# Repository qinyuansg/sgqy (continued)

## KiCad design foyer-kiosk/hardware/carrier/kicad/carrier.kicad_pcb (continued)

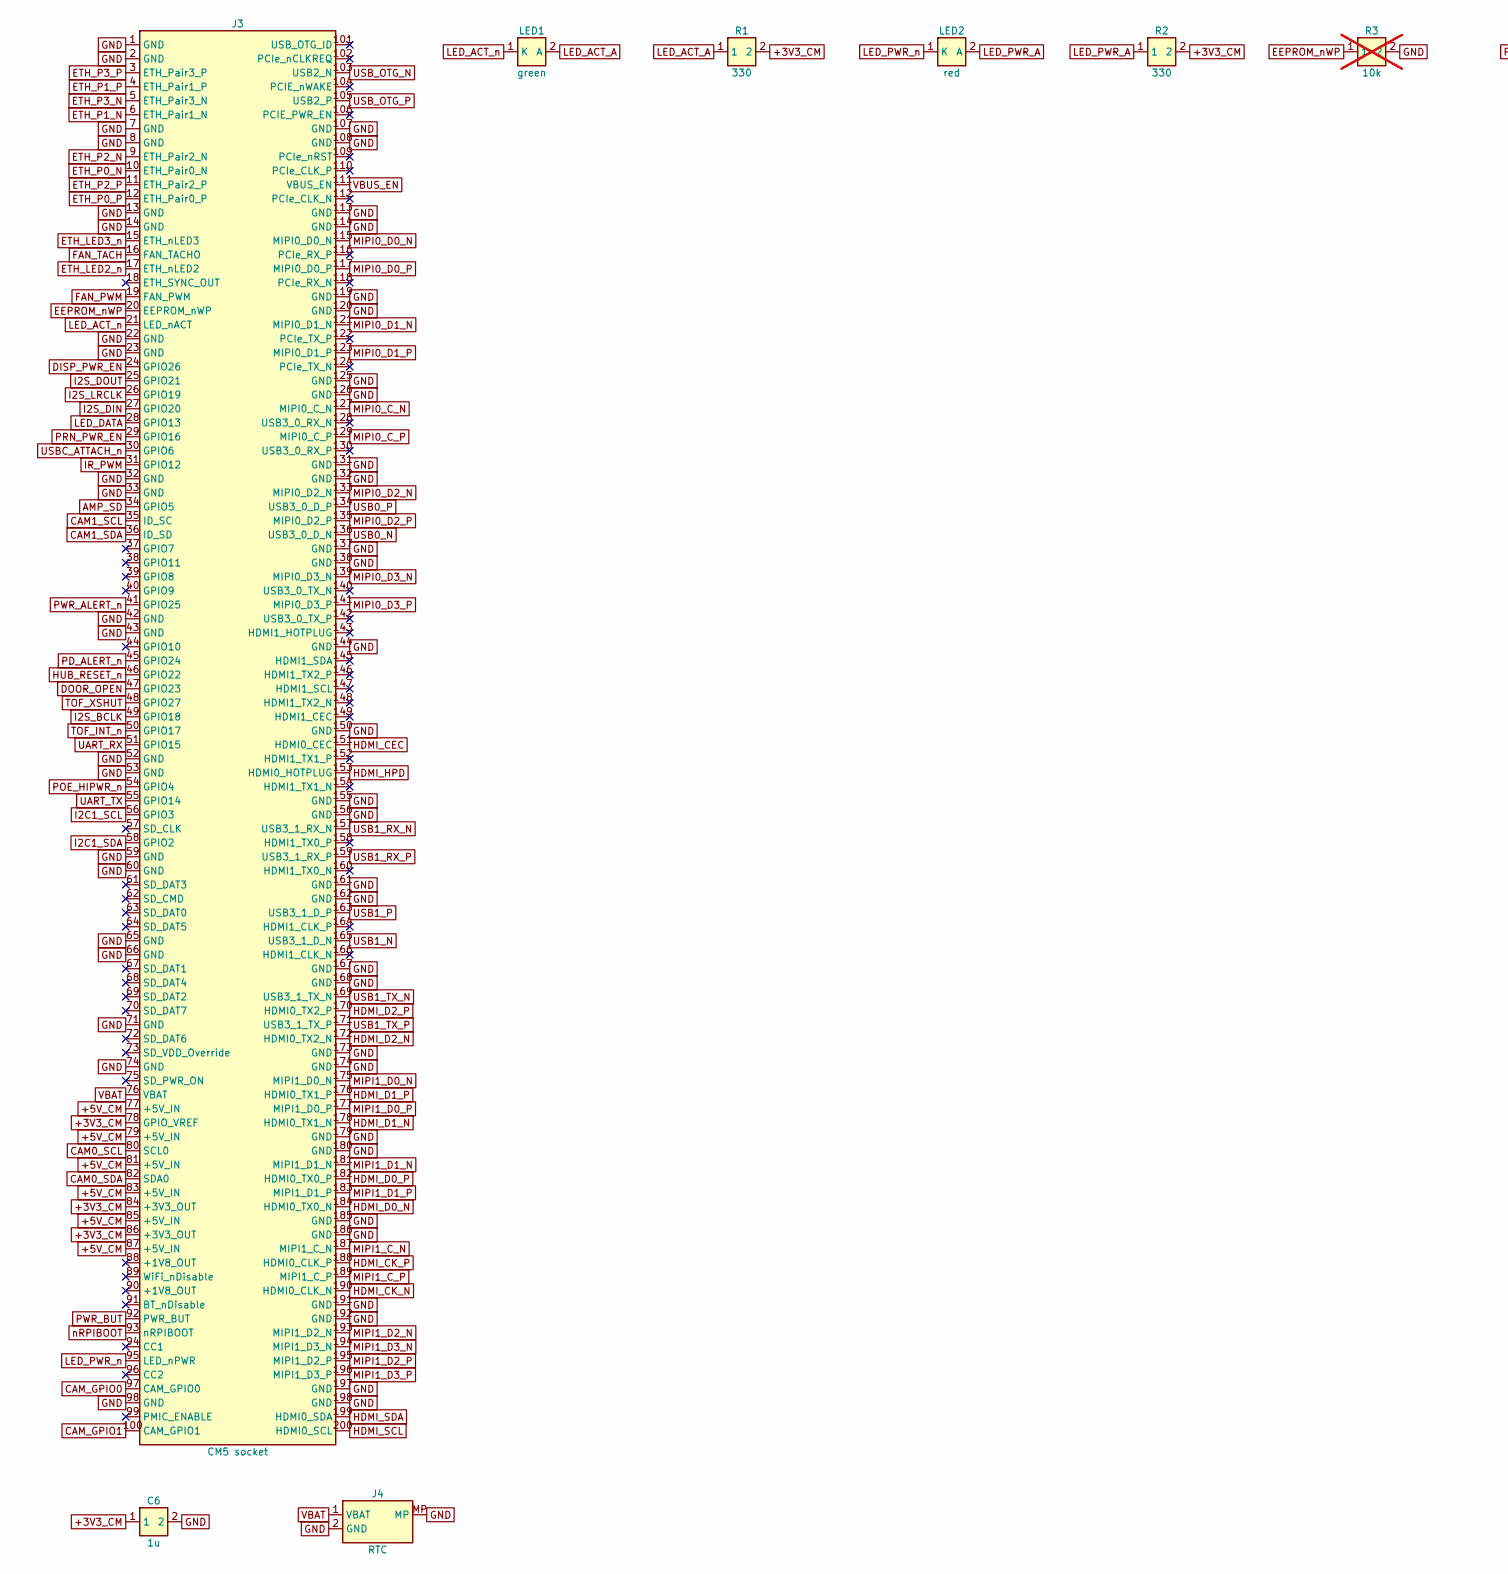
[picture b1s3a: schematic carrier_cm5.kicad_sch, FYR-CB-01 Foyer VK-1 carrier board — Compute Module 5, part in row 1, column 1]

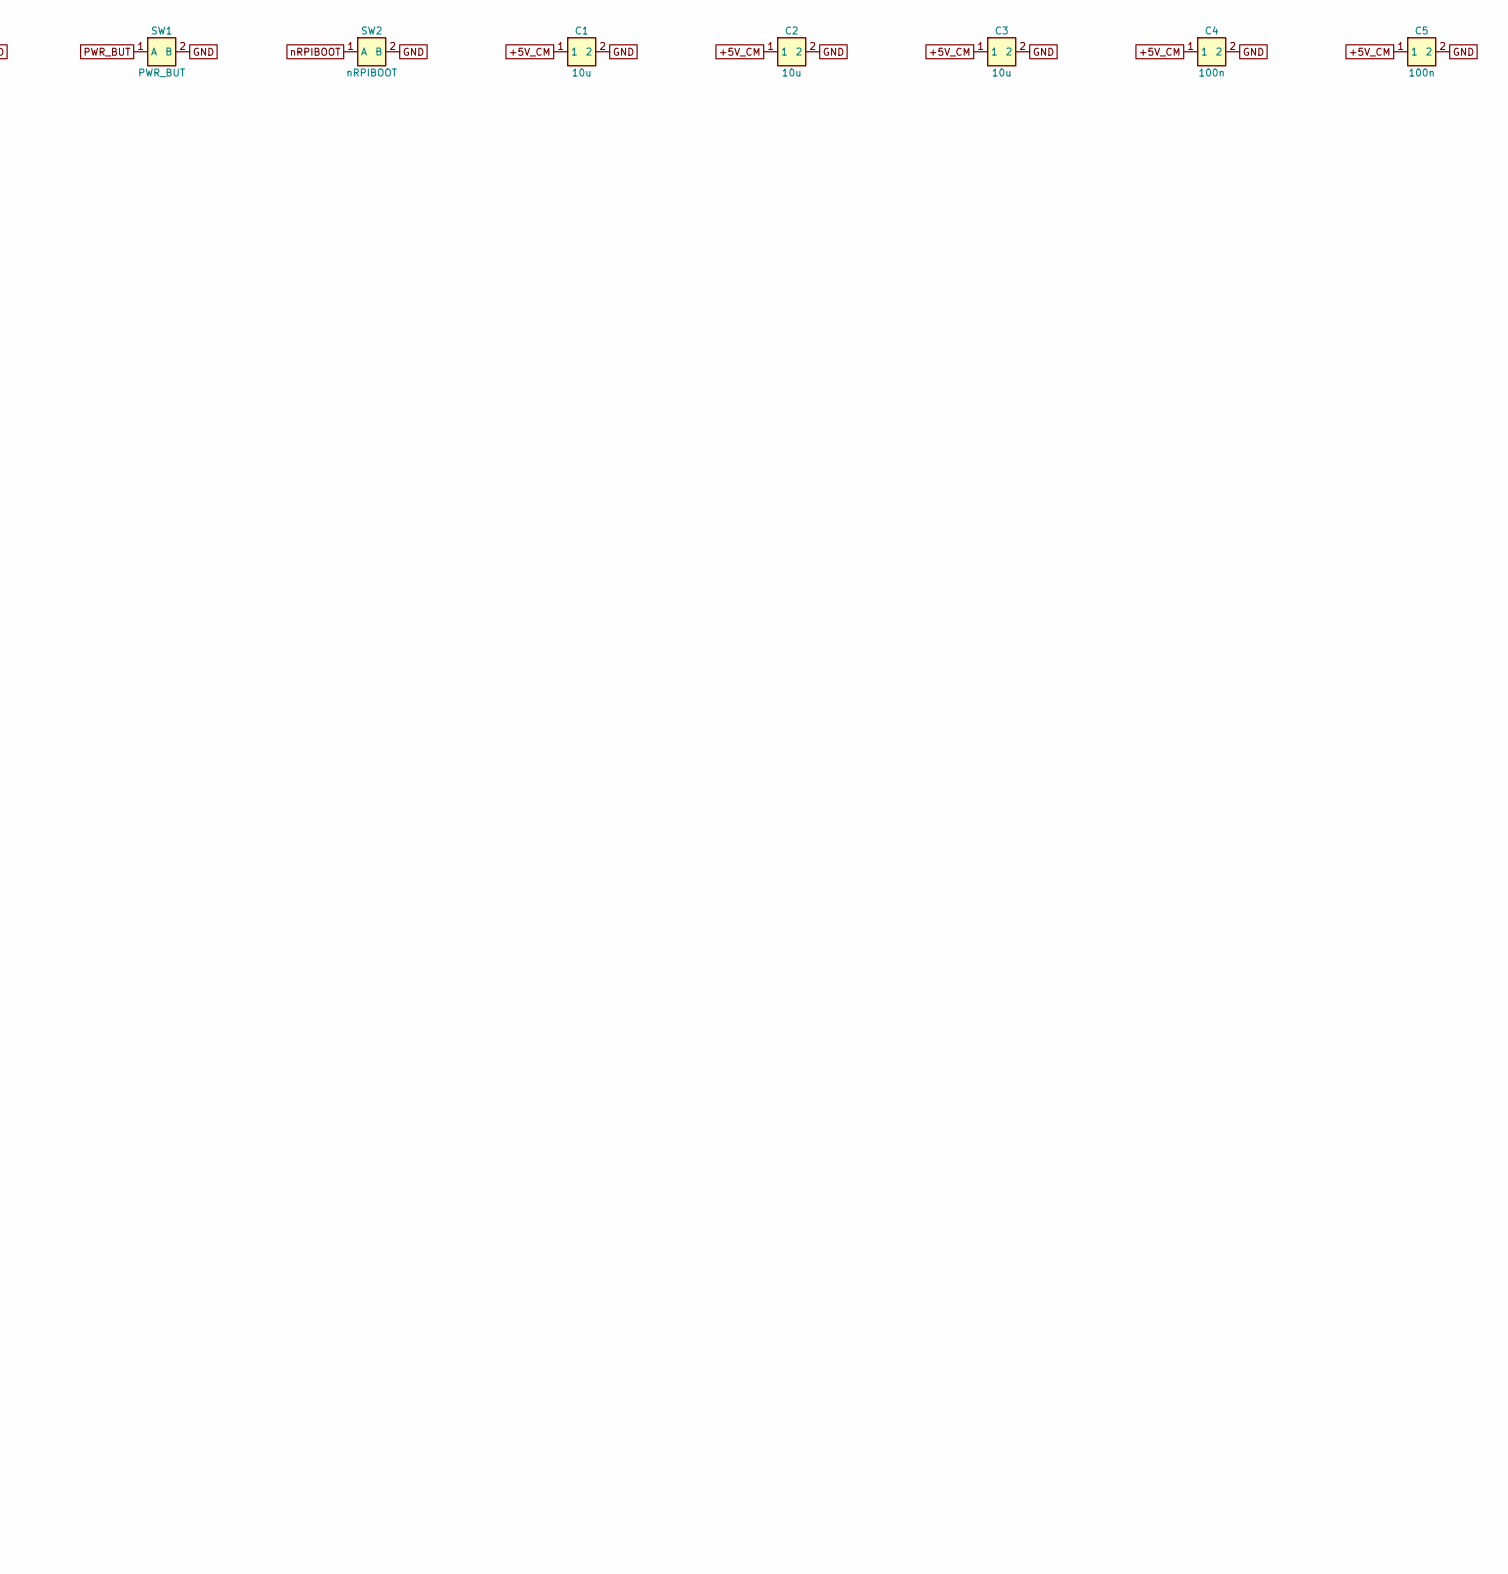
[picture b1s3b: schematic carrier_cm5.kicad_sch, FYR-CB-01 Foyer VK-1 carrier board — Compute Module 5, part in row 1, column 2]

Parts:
C1, C2, C3: 10u; C_0805_2012Metric
C4, C5: 100n; C_0805_2012Metric
C6: 1u; C_0402_1005Metric
J3: CM5 socket; RPi_CM5_DF40C-100DS_Pair; MPN DF40C-100DS-0.4V(51)
J4: RTC; JST_SH_SM02B-SRSS-TB_1x02-1MP_P1.00mm_Horizontal; MPN SM02B-SRSS-TB
LED1: green; LED_0603_1608Metric; MPN LTST-C191KGKT
LED2: red; LED_0603_1608Metric; MPN LTST-C191KRKT
R1, R2: 330; R_0402_1005Metric
R3: 10k; R_0402_1005Metric; not fitted
SW1: PWR_BUT; SW_Push_1P1T_NO_CK_KMR2; MPN KMR221GLFS
SW2: nRPIBOOT; SW_Push_1P1T_NO_CK_KMR2; MPN KMR221GLFS

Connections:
+3V3_CM: C6.1, J3.78 (GPIO_VREF), J3.84 (+3V3_OUT), J3.86 (+3V3_OUT), R1.2, R2.2; also elsewhere on the board
+5V_CM: C1.1, C2.1, C3.1, C4.1, C5.1, J3.77 (+5V_IN), J3.79 (+5V_IN), J3.81 (+5V_IN), J3.83 (+5V_IN), J3.85 (+5V_IN), J3.87 (+5V_IN); also elsewhere on the board
AMP_SD: J3.34 (GPIO5); also elsewhere on the board
CAM0_SCL: J3.80 (SCL0); also elsewhere on the board
CAM0_SDA: J3.82 (SDA0); also elsewhere on the board
CAM1_SCL: J3.35 (ID_SC); also elsewhere on the board
CAM1_SDA: J3.36 (ID_SD); also elsewhere on the board
CAM_GPIO0: J3.97 (CAM_GPIO0); also elsewhere on the board
CAM_GPIO1: J3.100 (CAM_GPIO1); also elsewhere on the board
DISP_PWR_EN: J3.24 (GPIO26); also elsewhere on the board
DOOR_OPEN: J3.47 (GPIO23); also elsewhere on the board
EEPROM_nWP: J3.20 (EEPROM_nWP), R3.1
ETH_LED2_n: J3.17 (ETH_nLED2); also elsewhere on the board
ETH_LED3_n: J3.15 (ETH_nLED3); also elsewhere on the board
ETH_P0_N: J3.10 (ETH_Pair0_N); also elsewhere on the board
ETH_P0_P: J3.12 (ETH_Pair0_P); also elsewhere on the board
ETH_P1_N: J3.6 (ETH_Pair1_N); also elsewhere on the board
ETH_P1_P: J3.4 (ETH_Pair1_P); also elsewhere on the board
ETH_P2_N: J3.9 (ETH_Pair2_N); also elsewhere on the board
ETH_P2_P: J3.11 (ETH_Pair2_P); also elsewhere on the board
ETH_P3_N: J3.5 (ETH_Pair3_N); also elsewhere on the board
ETH_P3_P: J3.3 (ETH_Pair3_P); also elsewhere on the board
FAN_PWM: J3.19 (FAN_PWM); also elsewhere on the board
FAN_TACH: J3.16 (FAN_TACHO); also elsewhere on the board
GND: C1.2, C2.2, C3.2, C4.2, C5.2, C6.2, J3.1 (GND), J3.2 (GND), J3.7 (GND), J3.8 (GND), J3.13 (GND), J3.14 (GND), J3.22 (GND), J3.23 (GND), J3.32 (GND), J3.33 (GND), J3.42 (GND), J3.43 (GND), J3.52 (GND), J3.53 (GND), J3.59 (GND), J3.60 (GND), J3.65 (GND), J3.66 (GND), J3.71 (GND), J3.74 (GND), J3.98 (GND), J3.107 (GND), J3.108 (GND), J3.113 (GND), J3.114 (GND), J3.119 (GND), J3.120 (GND), J3.125 (GND), J3.126 (GND), J3.131 (GND), J3.132 (GND), J3.137 (GND), J3.138 (GND), J3.144 (GND), J3.150 (GND), J3.155 (GND), J3.156 (GND), J3.161 (GND), J3.162 (GND), J3.167 (GND), J3.168 (GND), J3.173 (GND), J3.174 (GND), J3.179 (GND), J3.180 (GND), J3.185 (GND), J3.186 (GND), J3.191 (GND), J3.192 (GND), J3.197 (GND), J3.198 (GND), J4.2 (GND), J4.MP, R3.2, SW1.2 (B), SW2.2 (B); also elsewhere on the board
HDMI_CEC: J3.151 (HDMI0_CEC); also elsewhere on the board
HDMI_CK_N: J3.190 (HDMI0_CLK_N); also elsewhere on the board
HDMI_CK_P: J3.188 (HDMI0_CLK_P); also elsewhere on the board
HDMI_D0_N: J3.184 (HDMI0_TX0_N); also elsewhere on the board
HDMI_D0_P: J3.182 (HDMI0_TX0_P); also elsewhere on the board
HDMI_D1_N: J3.178 (HDMI0_TX1_N); also elsewhere on the board
HDMI_D1_P: J3.176 (HDMI0_TX1_P); also elsewhere on the board
HDMI_D2_N: J3.172 (HDMI0_TX2_N); also elsewhere on the board
HDMI_D2_P: J3.170 (HDMI0_TX2_P); also elsewhere on the board
HDMI_HPD: J3.153 (HDMI0_HOTPLUG); also elsewhere on the board
HDMI_SCL: J3.200 (HDMI0_SCL); also elsewhere on the board
HDMI_SDA: J3.199 (HDMI0_SDA); also elsewhere on the board
HUB_RESET_n: J3.46 (GPIO22); also elsewhere on the board
I2C1_SCL: J3.56 (GPIO3); also elsewhere on the board
I2C1_SDA: J3.58 (GPIO2); also elsewhere on the board
I2S_BCLK: J3.49 (GPIO18); also elsewhere on the board
I2S_DIN: J3.27 (GPIO20); also elsewhere on the board
I2S_DOUT: J3.25 (GPIO21); also elsewhere on the board
I2S_LRCLK: J3.26 (GPIO19); also elsewhere on the board
IR_PWM: J3.31 (GPIO12); also elsewhere on the board
LED_ACT_A: LED1.2 (A), R1.1
LED_ACT_n: J3.21 (LED_nACT), LED1.1 (K)
LED_DATA: J3.28 (GPIO13); also elsewhere on the board
LED_PWR_A: LED2.2 (A), R2.1
LED_PWR_n: J3.95 (LED_nPWR), LED2.1 (K)
MIPI0_C_N: J3.127 (MIPI0_C_N); also elsewhere on the board
MIPI0_C_P: J3.129 (MIPI0_C_P); also elsewhere on the board
MIPI0_D0_N: J3.115 (MIPI0_D0_N); also elsewhere on the board
MIPI0_D0_P: J3.117 (MIPI0_D0_P); also elsewhere on the board
MIPI0_D1_N: J3.121 (MIPI0_D1_N); also elsewhere on the board
MIPI0_D1_P: J3.123 (MIPI0_D1_P); also elsewhere on the board
MIPI0_D2_N: J3.133 (MIPI0_D2_N); also elsewhere on the board
MIPI0_D2_P: J3.135 (MIPI0_D2_P); also elsewhere on the board
MIPI0_D3_N: J3.139 (MIPI0_D3_N); also elsewhere on the board
MIPI0_D3_P: J3.141 (MIPI0_D3_P); also elsewhere on the board
MIPI1_C_N: J3.187 (MIPI1_C_N); also elsewhere on the board
MIPI1_C_P: J3.189 (MIPI1_C_P); also elsewhere on the board
MIPI1_D0_N: J3.175 (MIPI1_D0_N); also elsewhere on the board
MIPI1_D0_P: J3.177 (MIPI1_D0_P); also elsewhere on the board
MIPI1_D1_N: J3.181 (MIPI1_D1_N); also elsewhere on the board
MIPI1_D1_P: J3.183 (MIPI1_D1_P); also elsewhere on the board
MIPI1_D2_N: J3.193 (MIPI1_D2_N); also elsewhere on the board
MIPI1_D2_P: J3.195 (MIPI1_D2_P); also elsewhere on the board
MIPI1_D3_N: J3.194 (MIPI1_D3_N); also elsewhere on the board
MIPI1_D3_P: J3.196 (MIPI1_D3_P); also elsewhere on the board
PD_ALERT_n: J3.45 (GPIO24); also elsewhere on the board
POE_HIPWR_n: J3.54 (GPIO4); also elsewhere on the board
PRN_PWR_EN: J3.29 (GPIO16); also elsewhere on the board
PWR_ALERT_n: J3.41 (GPIO25); also elsewhere on the board
PWR_BUT: J3.92 (PWR_BUT), SW1.1 (A)
TOF_INT_n: J3.50 (GPIO17); also elsewhere on the board
TOF_XSHUT: J3.48 (GPIO27); also elsewhere on the board
UART_RX: J3.51 (GPIO15); also elsewhere on the board
UART_TX: J3.55 (GPIO14); also elsewhere on the board
USB0_N: J3.136 (USB3_0_D_N); also elsewhere on the board
USB0_P: J3.134 (USB3_0_D_P); also elsewhere on the board
USB1_N: J3.165 (USB3_1_D_N); also elsewhere on the board
USB1_P: J3.163 (USB3_1_D_P); also elsewhere on the board
USB1_RX_N: J3.157 (USB3_1_RX_N); also elsewhere on the board
USB1_RX_P: J3.159 (USB3_1_RX_P); also elsewhere on the board
USB1_TX_N: J3.169 (USB3_1_TX_N); also elsewhere on the board
USB1_TX_P: J3.171 (USB3_1_TX_P); also elsewhere on the board
USBC_ATTACH_n: J3.30 (GPIO6); also elsewhere on the board
USB_OTG_N: J3.103 (USB2_N); also elsewhere on the board
USB_OTG_P: J3.105 (USB2_P); also elsewhere on the board
VBAT: J3.76 (VBAT), J4.1 (VBAT)
VBUS_EN: J3.111 (VBUS_EN); also elsewhere on the board
nRPIBOOT: J3.93 (nRPIBOOT), SW2.1 (A)

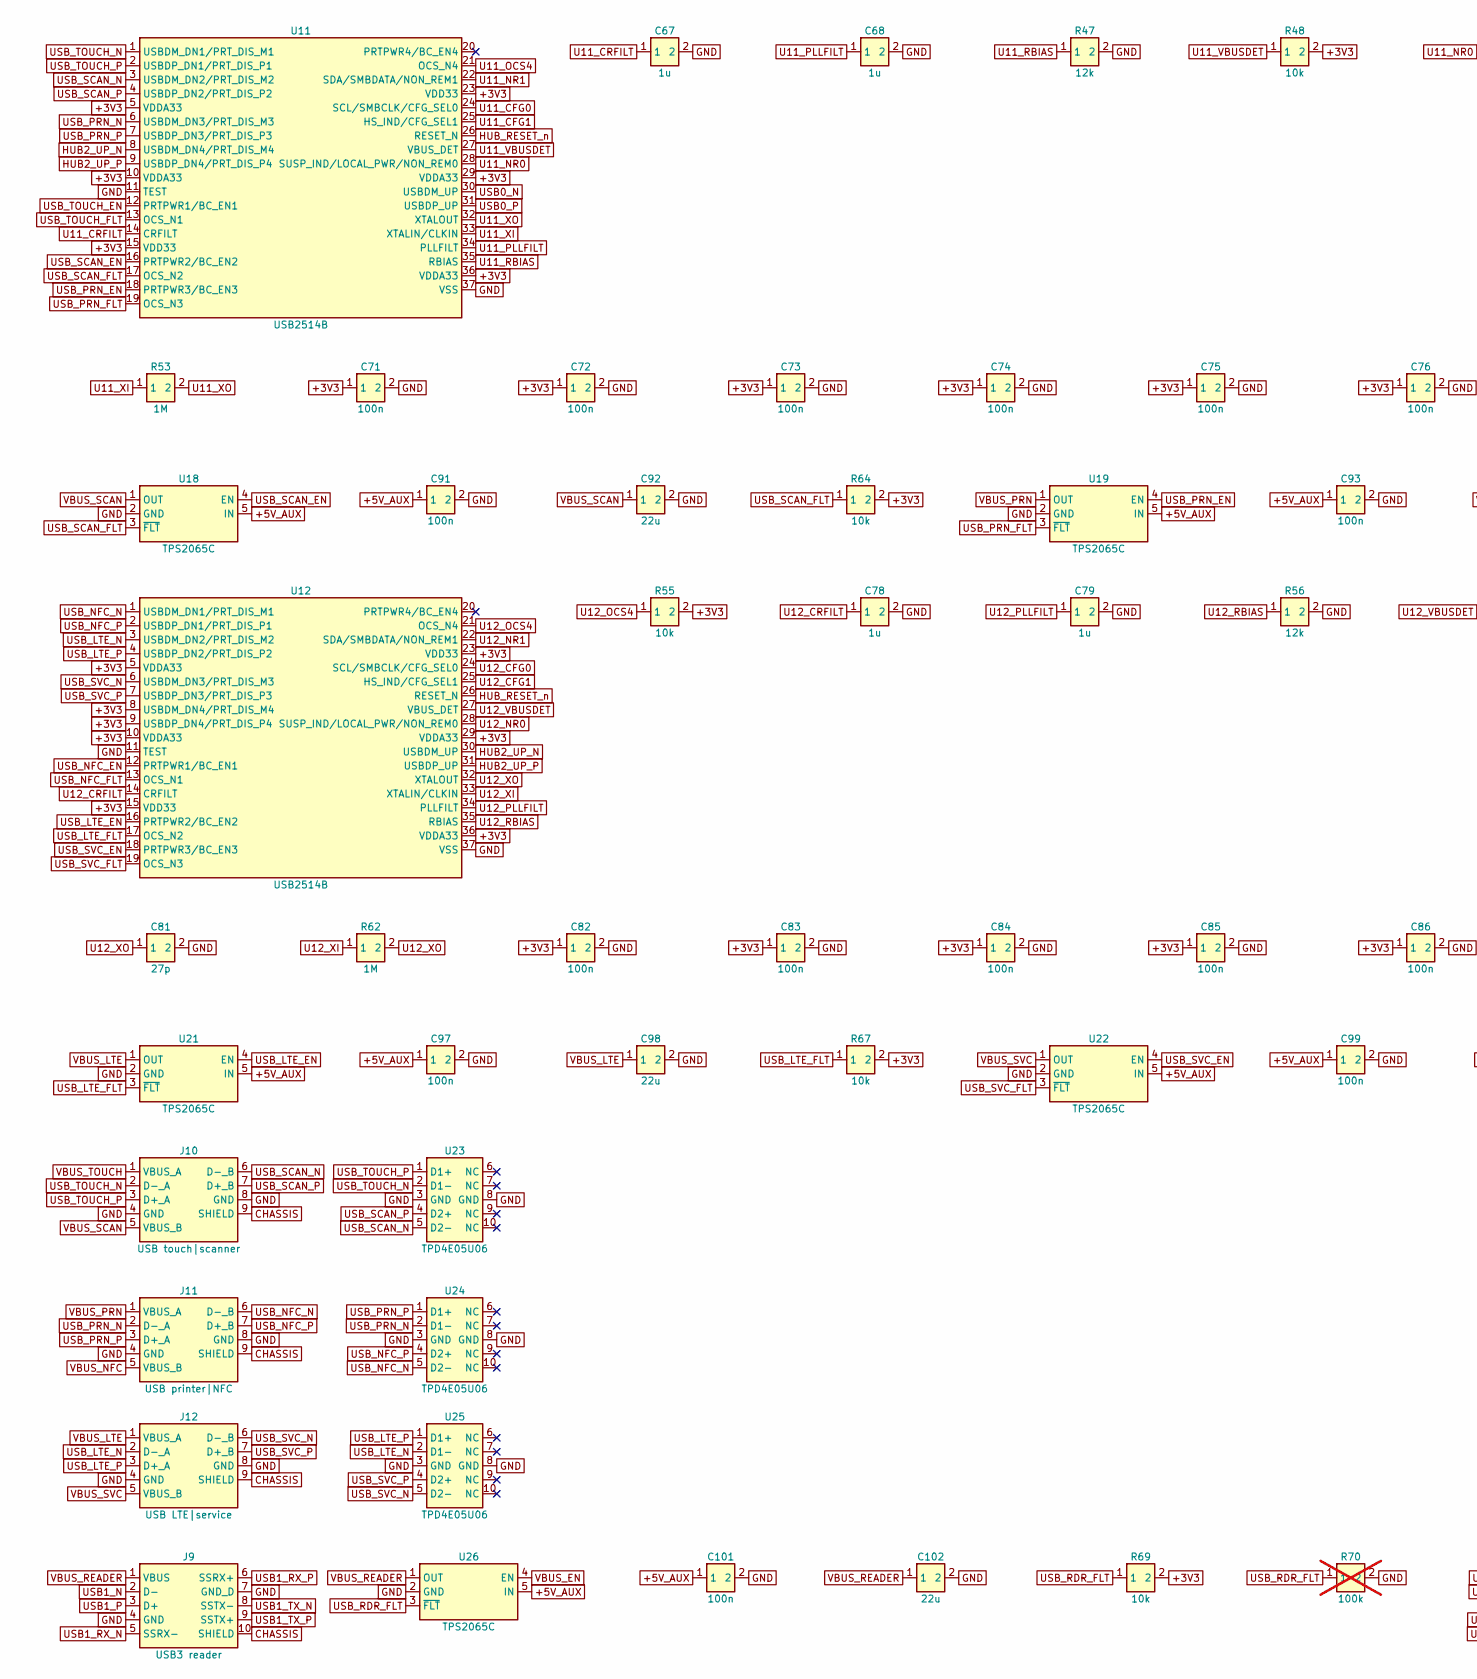
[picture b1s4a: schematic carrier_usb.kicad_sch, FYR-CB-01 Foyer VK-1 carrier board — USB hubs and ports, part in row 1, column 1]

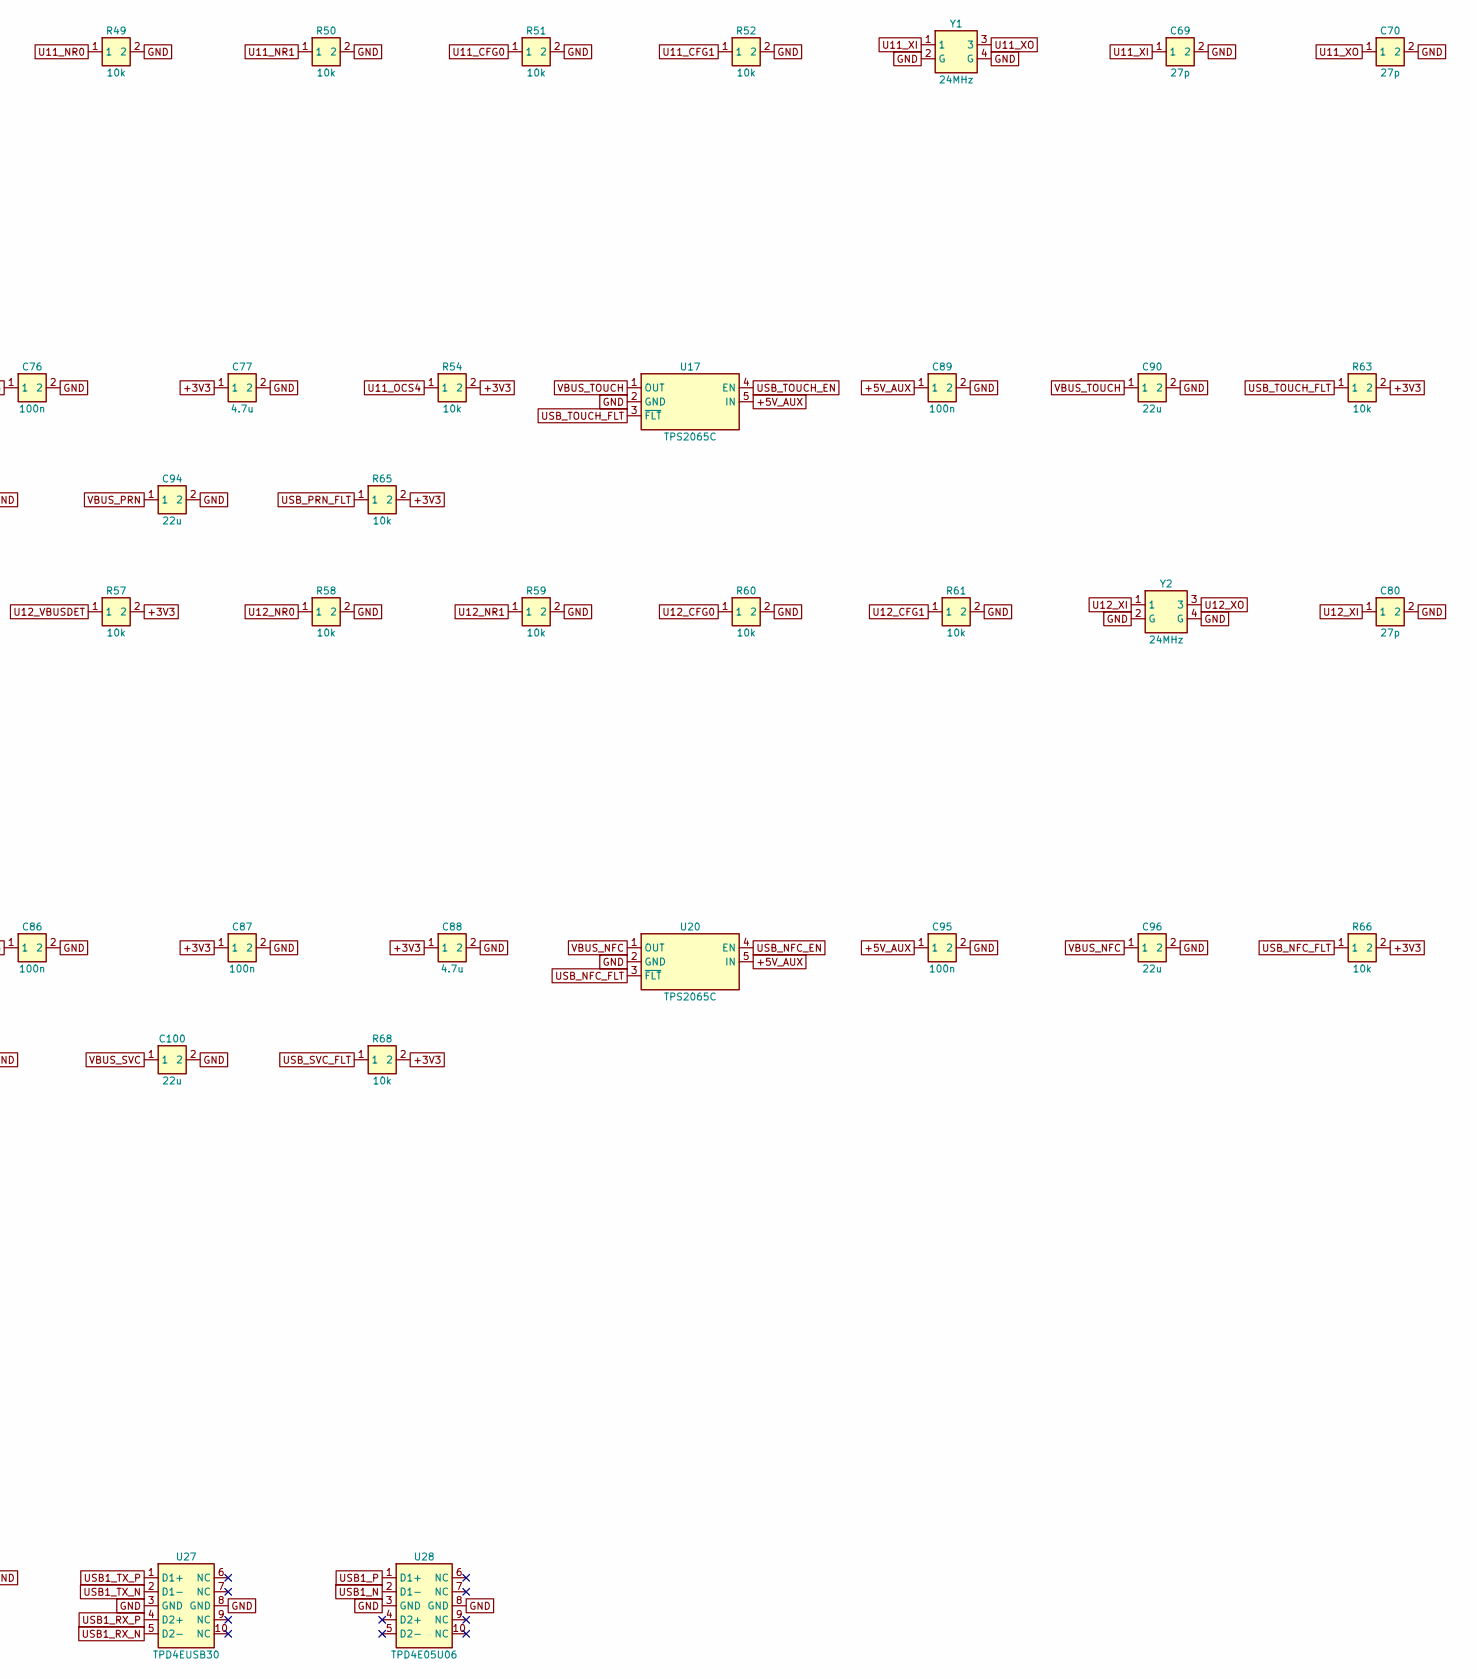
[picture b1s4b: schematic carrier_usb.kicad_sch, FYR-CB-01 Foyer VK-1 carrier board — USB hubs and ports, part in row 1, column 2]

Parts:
C67, C68, C78, C79: 1u; C_0402_1005Metric
C69, C70, C80, C81: 27p; C_0402_1005Metric
C71, C72, C73, C74, C75, C76, C82, C83, C84, C85, C86, C87, C89, C91, C93, C95, C97, C99, C101: 100n; C_0402_1005Metric
C77, C88: 4.7u; C_0603_1608Metric
C90, C92, C94, C96, C98, C100, C102: 22u; C_0805_2012Metric
J9: USB3 reader; USB3_A_Receptacle_Wuerth_692122030100; MPN 692122030100
J10: USB touch|scanner; USB_A_Wuerth_61400826021_Horizontal_Stacked; MPN 61400826021
J11: USB printer|NFC; USB_A_Wuerth_61400826021_Horizontal_Stacked; MPN 61400826021
J12: USB LTE|service; USB_A_Wuerth_61400826021_Horizontal_Stacked; MPN 61400826021
R47, R56: 12k; R_0402_1005Metric
R48, R49, R50, R51, R52, R54, R55, R57, R58, R59, R60, R61, R63, R64, R65, R66, R67, R68, R69: 10k; R_0402_1005Metric
R53, R62: 1M; R_0402_1005Metric
R70: 100k; R_0402_1005Metric; not fitted
U11, U12: USB2514B; QFN-36-1EP_6x6mm_P0.5mm_EP3.7x3.7mm; MPN USB2514B-AEZC-TR
U17, U18, U19, U20, U21, U22, U26: TPS2065C; SOT-23-5; MPN TPS2065CDBVR
U23, U24, U25, U28: TPD4E05U06; USON-10_2.5x1.0mm_P0.5mm; MPN TPD4E05U06DQAR
U27: TPD4EUSB30; USON-10_2.5x1.0mm_P0.5mm; MPN TPD4EUSB30DQAR
Y1, Y2: 24MHz; Crystal_SMD_3225-4Pin_3.2x2.5mm; MPN ABM8-24.000MHZ-B2-T

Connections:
+3V3: C71.1, C72.1, C73.1, C74.1, C75.1, C76.1, C77.1, C82.1, C83.1, C84.1, C85.1, C86.1, C87.1, C88.1, R48.2, R54.2, R55.2, R57.2, R63.2, R64.2, R65.2, R66.2, R67.2, R68.2, R69.2, U11.5 (VDDA33), U11.10 (VDDA33), U11.15 (VDD33), U11.23 (VDD33), U11.29 (VDDA33), U11.36 (VDDA33), U12.5 (VDDA33), U12.8 (USBDM_DN4/PRT_DIS_M4), U12.9 (USBDP_DN4/PRT_DIS_P4), U12.10 (VDDA33), U12.15 (VDD33), U12.23 (VDD33), U12.29 (VDDA33), U12.36 (VDDA33); also elsewhere on the board
+5V_AUX: C89.1, C91.1, C93.1, C95.1, C97.1, C99.1, C101.1, U17.5 (IN), U18.5 (IN), U19.5 (IN), U20.5 (IN), U21.5 (IN), U22.5 (IN), U26.5 (IN); also elsewhere on the board
CHASSIS: J9.10 (SHIELD), J10.9 (SHIELD), J11.9 (SHIELD), J12.9 (SHIELD); also elsewhere on the board
GND: C67.2, C68.2, C69.2, C70.2, C71.2, C72.2, C73.2, C74.2, C75.2, C76.2, C77.2, C78.2, C79.2, C80.2, C81.2, C82.2, C83.2, C84.2, C85.2, C86.2, C87.2, C88.2, C89.2, C90.2, C91.2, C92.2, C93.2, C94.2, C95.2, C96.2, C97.2, C98.2, C99.2, C100.2, C101.2, C102.2, J9.4 (GND), J9.7 (GND_D), J10.4 (GND), J10.8 (GND), J11.4 (GND), J11.8 (GND), J12.4 (GND), J12.8 (GND), R47.2, R49.2, R50.2, R51.2, R52.2, R56.2, R58.2, R59.2, R60.2, R61.2, R70.2, U11.11 (TEST), U11.37 (VSS), U12.11 (TEST), U12.37 (VSS), U17.2 (GND), U18.2 (GND), U19.2 (GND), U20.2 (GND), U21.2 (GND), U22.2 (GND), U23.3 (GND), U23.8 (GND), U24.3 (GND), U24.8 (GND), U25.3 (GND), U25.8 (GND), U26.2 (GND), U27.3 (GND), U27.8 (GND), U28.3 (GND), U28.8 (GND), Y1.2 (G), Y1.4 (G), Y2.2 (G), Y2.4 (G); also elsewhere on the board
HUB2_UP_N: U11.8 (USBDM_DN4/PRT_DIS_M4), U12.30 (USBDM_UP)
HUB2_UP_P: U11.9 (USBDP_DN4/PRT_DIS_P4), U12.31 (USBDP_UP)
HUB_RESET_n: U11.26 (RESET_N), U12.26 (RESET_N); also elsewhere on the board
U11_CFG0: R51.1, U11.24 (SCL/SMBCLK/CFG_SEL0)
U11_CFG1: R52.1, U11.25 (HS_IND/CFG_SEL1)
U11_CRFILT: C67.1, U11.14 (CRFILT)
U11_NR0: R49.1, U11.28 (SUSP_IND/LOCAL_PWR/NON_REM0)
U11_NR1: R50.1, U11.22 (SDA/SMBDATA/NON_REM1)
U11_OCS4: R54.1, U11.21 (OCS_N4)
U11_PLLFILT: C68.1, U11.34 (PLLFILT)
U11_RBIAS: R47.1, U11.35 (RBIAS)
U11_VBUSDET: R48.1, U11.27 (VBUS_DET)
U11_XI: C69.1, R53.1, U11.33 (XTALIN/CLKIN), Y1.1
U11_XO: C70.1, R53.2, U11.32 (XTALOUT), Y1.3
U12_CFG0: R60.1, U12.24 (SCL/SMBCLK/CFG_SEL0)
U12_CFG1: R61.1, U12.25 (HS_IND/CFG_SEL1)
U12_CRFILT: C78.1, U12.14 (CRFILT)
U12_NR0: R58.1, U12.28 (SUSP_IND/LOCAL_PWR/NON_REM0)
U12_NR1: R59.1, U12.22 (SDA/SMBDATA/NON_REM1)
U12_OCS4: R55.1, U12.21 (OCS_N4)
U12_PLLFILT: C79.1, U12.34 (PLLFILT)
U12_RBIAS: R56.1, U12.35 (RBIAS)
U12_VBUSDET: R57.1, U12.27 (VBUS_DET)
U12_XI: C80.1, R62.1, U12.33 (XTALIN/CLKIN), Y2.1
U12_XO: C81.1, R62.2, U12.32 (XTALOUT), Y2.3
USB0_N: U11.30 (USBDM_UP); also elsewhere on the board
USB0_P: U11.31 (USBDP_UP); also elsewhere on the board
USB1_N: J9.2 (D-), U28.2 (D1-); also elsewhere on the board
USB1_P: J9.3 (D+), U28.1 (D1+); also elsewhere on the board
USB1_RX_N: J9.5 (SSRX-), U27.5 (D2-); also elsewhere on the board
USB1_RX_P: J9.6 (SSRX+), U27.4 (D2+); also elsewhere on the board
USB1_TX_N: J9.8 (SSTX-), U27.2 (D1-); also elsewhere on the board
USB1_TX_P: J9.9 (SSTX+), U27.1 (D1+); also elsewhere on the board
USB_LTE_EN: U12.16 (PRTPWR2/BC_EN2), U21.4 (EN)
USB_LTE_FLT: R67.1, U12.17 (OCS_N2), U21.3 (~FLT)
USB_LTE_N: J12.2 (D-_A), U12.3 (USBDM_DN2/PRT_DIS_M2), U25.2 (D1-)
USB_LTE_P: J12.3 (D+_A), U12.4 (USBDP_DN2/PRT_DIS_P2), U25.1 (D1+)
USB_NFC_EN: U12.12 (PRTPWR1/BC_EN1), U20.4 (EN)
USB_NFC_FLT: R66.1, U12.13 (OCS_N1), U20.3 (~FLT)
USB_NFC_N: J11.6 (D-_B), U12.1 (USBDM_DN1/PRT_DIS_M1), U24.5 (D2-)
USB_NFC_P: J11.7 (D+_B), U12.2 (USBDP_DN1/PRT_DIS_P1), U24.4 (D2+)
USB_PRN_EN: U11.18 (PRTPWR3/BC_EN3), U19.4 (EN)
USB_PRN_FLT: R65.1, U11.19 (OCS_N3), U19.3 (~FLT)
USB_PRN_N: J11.2 (D-_A), U11.6 (USBDM_DN3/PRT_DIS_M3), U24.2 (D1-)
USB_PRN_P: J11.3 (D+_A), U11.7 (USBDP_DN3/PRT_DIS_P3), U24.1 (D1+)
USB_RDR_FLT: R69.1, R70.1, U26.3 (~FLT)
USB_SCAN_EN: U11.16 (PRTPWR2/BC_EN2), U18.4 (EN)
USB_SCAN_FLT: R64.1, U11.17 (OCS_N2), U18.3 (~FLT)
USB_SCAN_N: J10.6 (D-_B), U11.3 (USBDM_DN2/PRT_DIS_M2), U23.5 (D2-)
USB_SCAN_P: J10.7 (D+_B), U11.4 (USBDP_DN2/PRT_DIS_P2), U23.4 (D2+)
USB_SVC_EN: U12.18 (PRTPWR3/BC_EN3), U22.4 (EN)
USB_SVC_FLT: R68.1, U12.19 (OCS_N3), U22.3 (~FLT)
USB_SVC_N: J12.6 (D-_B), U12.6 (USBDM_DN3/PRT_DIS_M3), U25.5 (D2-)
USB_SVC_P: J12.7 (D+_B), U12.7 (USBDP_DN3/PRT_DIS_P3), U25.4 (D2+)
USB_TOUCH_EN: U11.12 (PRTPWR1/BC_EN1), U17.4 (EN)
USB_TOUCH_FLT: R63.1, U11.13 (OCS_N1), U17.3 (~FLT)
USB_TOUCH_N: J10.2 (D-_A), U11.1 (USBDM_DN1/PRT_DIS_M1), U23.2 (D1-)
USB_TOUCH_P: J10.3 (D+_A), U11.2 (USBDP_DN1/PRT_DIS_P1), U23.1 (D1+)
VBUS_EN: U26.4 (EN); also elsewhere on the board
VBUS_LTE: C98.1, J12.1 (VBUS_A), U21.1 (OUT)
VBUS_NFC: C96.1, J11.5 (VBUS_B), U20.1 (OUT)
VBUS_PRN: C94.1, J11.1 (VBUS_A), U19.1 (OUT)
VBUS_READER: C102.1, J9.1 (VBUS), U26.1 (OUT)
VBUS_SCAN: C92.1, J10.5 (VBUS_B), U18.1 (OUT)
VBUS_SVC: C100.1, J12.5 (VBUS_B), U22.1 (OUT)
VBUS_TOUCH: C90.1, J10.1 (VBUS_A), U17.1 (OUT)

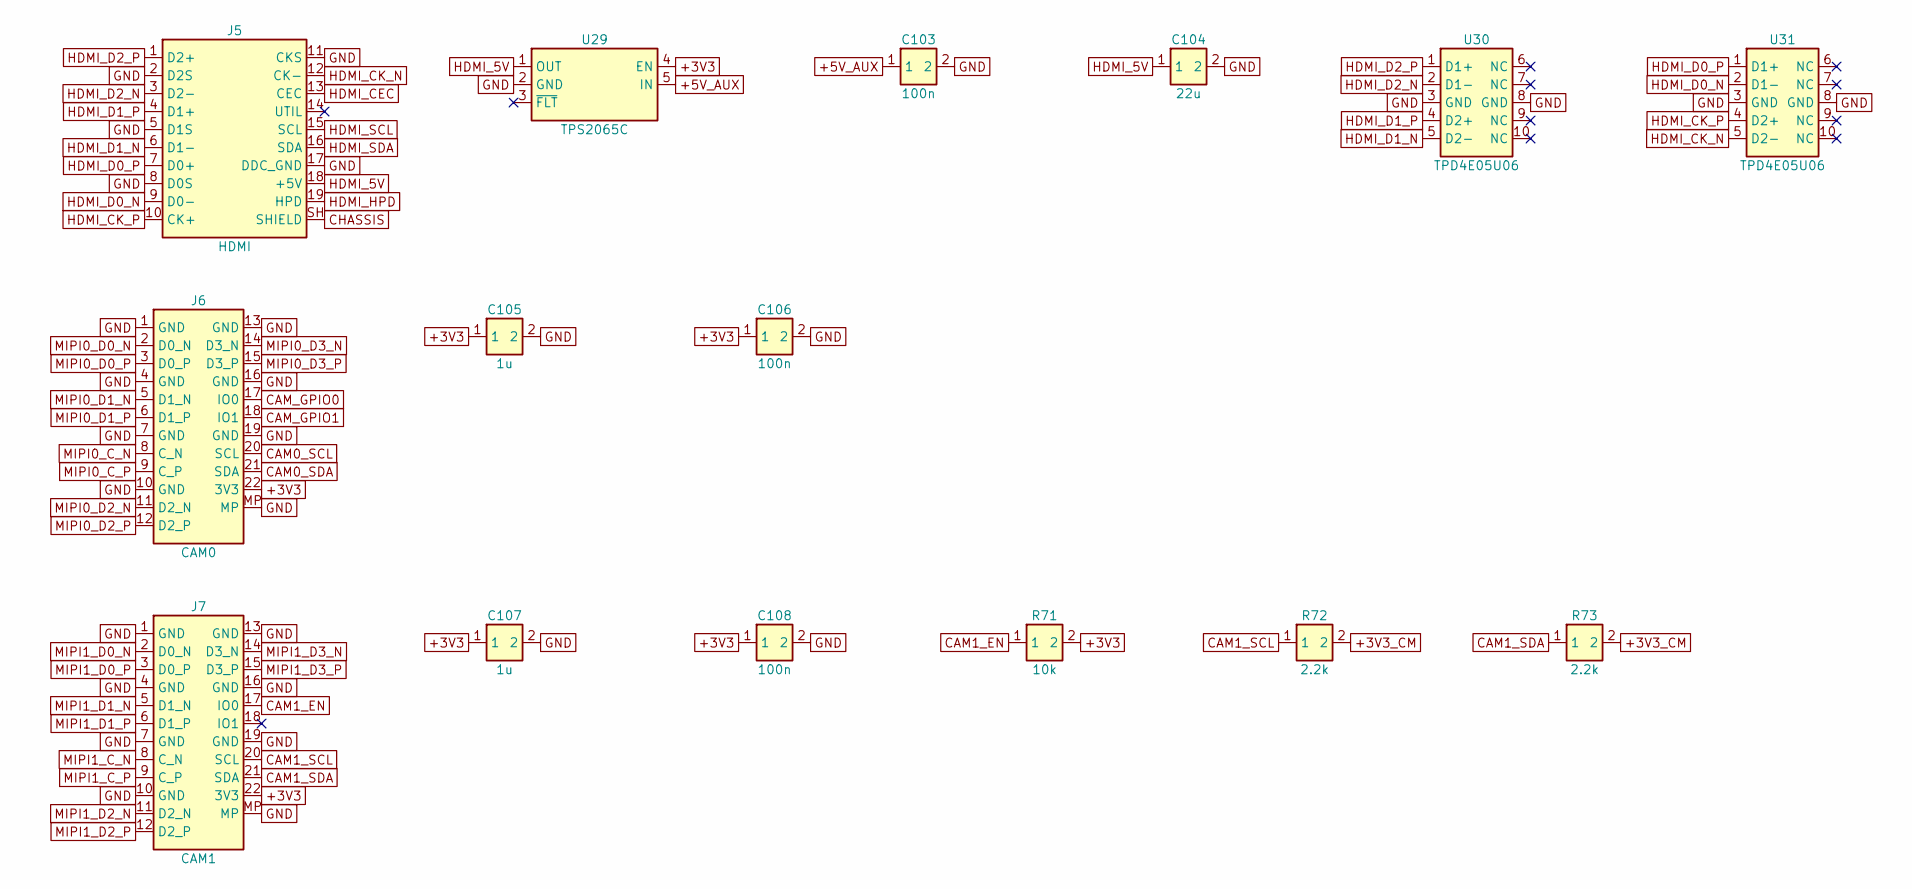
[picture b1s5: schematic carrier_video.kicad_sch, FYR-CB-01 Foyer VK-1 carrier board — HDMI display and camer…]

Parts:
C103, C106, C108: 100n; C_0402_1005Metric
C104: 22u; C_0805_2012Metric
C105, C107: 1u; C_0402_1005Metric
J5: HDMI; HDMI_A_Amphenol_10029449-x01xLF_Horizontal; MPN 10029449-111RLF
J6: CAM0; Hirose_FH12-22S-0.5SH_1x22-1MP_P0.50mm_Horizontal; MPN FH12-22S-0.5SH(55)
J7: CAM1; Hirose_FH12-22S-0.5SH_1x22-1MP_P0.50mm_Horizontal; MPN FH12-22S-0.5SH(55)
R71: 10k; R_0402_1005Metric
R72, R73: 2.2k; R_0402_1005Metric
U29: TPS2065C; SOT-23-5; MPN TPS2065CDBVR
U30, U31: TPD4E05U06; USON-10_2.5x1.0mm_P0.5mm; MPN TPD4E05U06DQAR

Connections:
+3V3: C105.1, C106.1, C107.1, C108.1, J6.22 (3V3), J7.22 (3V3), R71.2, U29.4 (EN); also elsewhere on the board
+3V3_CM: R72.2, R73.2; also elsewhere on the board
+5V_AUX: C103.1, U29.5 (IN); also elsewhere on the board
CAM0_SCL: J6.20 (SCL); also elsewhere on the board
CAM0_SDA: J6.21 (SDA); also elsewhere on the board
CAM1_EN: J7.17 (IO0), R71.1
CAM1_SCL: J7.20 (SCL), R72.1; also elsewhere on the board
CAM1_SDA: J7.21 (SDA), R73.1; also elsewhere on the board
CAM_GPIO0: J6.17 (IO0); also elsewhere on the board
CAM_GPIO1: J6.18 (IO1); also elsewhere on the board
CHASSIS: J5.SH (SHIELD); also elsewhere on the board
GND: C103.2, C104.2, C105.2, C106.2, C107.2, C108.2, J5.2 (D2S), J5.5 (D1S), J5.8 (D0S), J5.11 (CKS), J5.17 (DDC_GND), J6.1 (GND), J6.4 (GND), J6.7 (GND), J6.10 (GND), J6.13 (GND), J6.16 (GND), J6.19 (GND), J6.MP, J7.1 (GND), J7.4 (GND), J7.7 (GND), J7.10 (GND), J7.13 (GND), J7.16 (GND), J7.19 (GND), J7.MP, U29.2 (GND), U30.3 (GND), U30.8 (GND), U31.3 (GND), U31.8 (GND); also elsewhere on the board
HDMI_5V: C104.1, J5.18 (+5V), U29.1 (OUT)
HDMI_CEC: J5.13 (CEC); also elsewhere on the board
HDMI_CK_N: J5.12 (CK-), U31.5 (D2-); also elsewhere on the board
HDMI_CK_P: J5.10 (CK+), U31.4 (D2+); also elsewhere on the board
HDMI_D0_N: J5.9 (D0-), U31.2 (D1-); also elsewhere on the board
HDMI_D0_P: J5.7 (D0+), U31.1 (D1+); also elsewhere on the board
HDMI_D1_N: J5.6 (D1-), U30.5 (D2-); also elsewhere on the board
HDMI_D1_P: J5.4 (D1+), U30.4 (D2+); also elsewhere on the board
HDMI_D2_N: J5.3 (D2-), U30.2 (D1-); also elsewhere on the board
HDMI_D2_P: J5.1 (D2+), U30.1 (D1+); also elsewhere on the board
HDMI_HPD: J5.19 (HPD); also elsewhere on the board
HDMI_SCL: J5.15 (SCL); also elsewhere on the board
HDMI_SDA: J5.16 (SDA); also elsewhere on the board
MIPI0_C_N: J6.8 (C_N); also elsewhere on the board
MIPI0_C_P: J6.9 (C_P); also elsewhere on the board
MIPI0_D0_N: J6.2 (D0_N); also elsewhere on the board
MIPI0_D0_P: J6.3 (D0_P); also elsewhere on the board
MIPI0_D1_N: J6.5 (D1_N); also elsewhere on the board
MIPI0_D1_P: J6.6 (D1_P); also elsewhere on the board
MIPI0_D2_N: J6.11 (D2_N); also elsewhere on the board
MIPI0_D2_P: J6.12 (D2_P); also elsewhere on the board
MIPI0_D3_N: J6.14 (D3_N); also elsewhere on the board
MIPI0_D3_P: J6.15 (D3_P); also elsewhere on the board
MIPI1_C_N: J7.8 (C_N); also elsewhere on the board
MIPI1_C_P: J7.9 (C_P); also elsewhere on the board
MIPI1_D0_N: J7.2 (D0_N); also elsewhere on the board
MIPI1_D0_P: J7.3 (D0_P); also elsewhere on the board
MIPI1_D1_N: J7.5 (D1_N); also elsewhere on the board
MIPI1_D1_P: J7.6 (D1_P); also elsewhere on the board
MIPI1_D2_N: J7.11 (D2_N); also elsewhere on the board
MIPI1_D2_P: J7.12 (D2_P); also elsewhere on the board
MIPI1_D3_N: J7.14 (D3_N); also elsewhere on the board
MIPI1_D3_P: J7.15 (D3_P); also elsewhere on the board
